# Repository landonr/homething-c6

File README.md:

<p align="center">
  <picture>
    <source media="(prefers-color-scheme: dark)" srcset="docs/readme-assets/homeThingLogoWhite.svg">
    
  </picture>
</p>

<h1 align="center">homeThing C6</h1>

<p align="center">
  An open source universal remote that can control anything.<br>
  For your TV, Sonos, Zigbee lights, and Home Assistant. No touchscreen, no apps, no daily charging.
</p>

<p align="center">
  <a href="https://landonr.github.io/homething-c6/"><b>landonr.github.io/homething-c6</b></a>
</p>

<p align="center">

</p>

<p align="center">
  <sub>Prototype and fab costs sponsored by <a href="https://pcbway.com/g/Xymq6O">PCBWay</a>. Boards arrive fully assembled, no soldering required.</sub>
  <br>
  
</p>

<p align="center"><sub>One button lights the fireplace, another controls the lights, and the rest control the TV. <a href="https://landonr.github.io/homething-c6/">Learn more</a></sub></p>

## What homeThing C6 does

- **Runs your TV.** It learns the IR codes from the remote you already have. Then the wheel and pad drive the TV.
- **Switches the lights.** A button talks straight to Zigbee lights and groups.
- **Any button, any device.** Each button can drive something different, for example a gas fireplace over Zigbee.
- **Sleeps on its own.** It sleeps between presses, with a target of about a month per charge.
- **No hub needed.** Presses go straight to your Zigbee lights and IR devices. They work without Wi-Fi, Home Assistant, or Zigbee2MQTT.
- **No flashing needed.** Set every button from the remote's own web page, in any browser. You do not edit YAML or rebuild the firmware.
- **Bluetooth keys too.** Pair it like a Bluetooth keyboard or gamepad, and send media keys to a computer, phone, or tablet.
- **Open source, all of it.** The board, the case, and the ESPHome firmware are in this repository.

## Specs

### One remote, no screen.

| Spec | Detail |
| --- | --- |
| **Controls** | Scroll wheel with 5-way pad, 11 assignable buttons |
| **Battery** | 1000 mAh LiPo, with a target of about a month per charge |
| **Charging** | USB-C |
| **Processor** | Seeed Studio XIAO ESP32-C6 |
| **Infrared** | Transmits, receives, and learns codes |
| **Status** | 6 RGB LEDs |
| **Case** | 3D printed, SLA or FDM |
| **Wireless** | Wi-Fi, BLE, Zigbee |

## Build one, or get one ready to go

The board arrives fully assembled, so there is no soldering. The board design, the firmware, and the case files are all open source in this repository, so you can build your own from scratch.

- **Case:** The [`case/` README](case/README.md) documents the enclosure files and assembly information.
- **Board:** The [`c6remote-kicad/` README](c6remote-kicad/README.md) documents the KiCad hardware source.
- **Firmware:** The [Make It Yours](#make-it-yours) section documents button assignment. [`c6remote.yaml`](c6remote.yaml) is the ESPHome configuration.
- **Scripts:** The [`scripts/` README](scripts/README.md) documents project utilities and generated assets.

<p align="center"><sub>V2 board and case</sub></p>

## Your smart home, on real buttons

### Control Anything

Pick it up, press a button, and the lights change. No phone to unlock, no app to open.

- **TV:** Learns the IR codes from the remote you already have, then sends them.
- **Music:** Controls Sonos over Wi-Fi, or pairs with a phone, tablet, or computer over BLE for media keys.
- **Lights:** Talks straight to Zigbee lights and groups.
- **Home Assistant:** Puts any action or script on a button.

<p align="center">
  <picture>
    <source media="(prefers-color-scheme: dark)" srcset="docs/readme-assets/remote-controls-annotated-dark.svg">
    
  </picture>
  <picture>
    <source media="(prefers-color-scheme: dark)" srcset="docs/readme-assets/remote-back-annotated-dark.svg">
    
  </picture>
</p>

## Make It Yours

### Every button is yours to set.

Open the remote's own web page from any browser on your network. Pick a button, then pick what it does: an IR code, a Zigbee light or group, a BLE media key, or a Home Assistant action. You can also assign buttons on the remote itself. No app, no cloud.

#### Button assignment ([more info](RECEIVER.md))

Open `http://homething-c6-xxxxxx.local/` in a browser. `xxxxxx` is the end of the remote's MAC address.
Home Assistant also shows this address as the **Web Page** entity.
To assign buttons on the remote itself, hold `SW9` for two seconds.
[`RECEIVER.md`](RECEIVER.md) has the full steps.
The page has no password, so use it only on a trusted network.

<p align="center"><sub>The Buttons tab with a Zigbee assignment, and the Config tab</sub></p>

## Built Your Way

### Case ([more info](case/README.md))

- Parametric 3D printed case in three versions: FDM, SLA, and SLA one-piece.
- The flat FDM front needs no support on its face.
- The SLA front has a shallow dish around the keys and the wheel. A translucent ring insert carries the light of the status LEDs.
- The SLA one-piece front is the SLA front with the ring insert fused in. It prints in clear resin, so the whole front glows.
- Optional Qwiic access: a flush cover with two breakaway bridges stays in place until you need the port.
- Assembly needs one M2 x 5 pan head screw at the grip end.

<p align="center"><sub>SLA front face</sub></p>

### Board ([more info](c6remote-kicad/README.md))

- Custom PCB built around the Seeed Studio XIAO ESP32-C6.
- Sleeps between presses and wakes on any button.

<p align="center">
  <picture>
    <source media="(prefers-color-scheme: dark)" srcset="docs/readme-assets/board-front-annotated-dark.svg">
    
  </picture>
  <picture>
    <source media="(prefers-color-scheme: dark)" srcset="docs/readme-assets/board-back-annotated-dark.svg">
    
  </picture>
</p>
<p align="center"><sub>PCB front and back</sub></p>

<p align="center"><sub>Copper top and bottom</sub></p>

| Ref | Part | Role |
| --- | --- | --- |
| `U1` | [Seeed Studio XIAO ESP32-C6](https://mm.digikey.com/Volume0/opasdata/d220001/medias/docus/8932/102010636.pdf) | Main module: Wi-Fi, BLE, Zigbee/Thread |
| `MK1` | [DMM-4026-B-I2S-R I2S microphone](https://api.puiaudio.com/filename/DMM-4026-B-I2S-R.pdf) | Audio input: PUI Audio bottom-port MEMS part on the back copper, hearing through a 0.5mm NPTH. `LR` and `CONFIG` tie to ground for left-channel output, `C5` decouples VDD and `R12` pulls `sd` down. It replaced the ICS-43434 on 2026-09-07, after three of the five rev-B microphones failed |
| `U2` | [TSOP6136 IR receiver](https://www.vishay.com/docs/82457/tsop61.pdf) | IR receive: Vishay Panhead SMD part on the back copper, listening out the top end wall. AGC1, the most permissive of Vishay's settings, which is what lets `remote_receiver` learn arbitrary remotes. VDD sits on the switched `ir_vdd` rail rather than straight on `+3.3V`, gated by `Q3` below |
| `D1`, `Q1` | [INL-3AHIR30 IR LED](http://www.inolux-corp.com/datasheet/IR/Emitter/3mm%20Lamp/INL-3AHIR30_V1.0.pdf) driven by [MMBT2222A](https://assets.nexperia.com/documents/data-sheet/MMBT2222A.pdf) | IR transmit; D1 leads hand-bent 90° to fire through the top-edge notch (see `BEND 90°` silk mark) |
| `U3` | [PCF8575DBR I2C GPIO expander](https://www.ti.com/lit/ds/symlink/pcf8575.pdf) | Button input fan-out |
| `SW1`–`SW11` | [TL3315NF160Q tactile switches](https://www.e-switch.com/wp-content/uploads/2022/06/TL3315.pdf) | Discrete buttons |
| `ENC1` | [Adafruit ANO rotary encoder](https://cdn-learn.adafruit.com/assets/assets/000/104/942/original/tsw.pdf) | Scroll wheel: encoder channels plus five switch signals |
| `D2`–`D7` | [XL-2020RGBC-WS2812B addressable LEDs](https://mm.digikey.com/Volume0/opasdata/d220001/medias/docus/8903/5962_XL-2020RGBC-WS2812B.pdf) | Status light ring of 6 round the scroll wheel, WS2812B protocol: `GPIO17` drives `D2` DIN, and DOUT cascades clockwise through `D3`, `D6`, `D4`, and `D5` to `D7`. VDD sits on the switched `led_vdd` rail rather than straight on `+3.3V`, gated by `Q2` below, with `C4` as the only bulk cap on the chain (see [`docs/timeline.md`](docs/timeline.md)) |
| `Q2`, `R10`, `C4` | [AO3401A P-channel MOSFET](https://www.aosmd.com/res/datasheets/AO3401A.pdf), 1M 0603 pull-up, 1µF X7R 0805 cap | LED rail load switch: high-side `Q2` gates `+3.3V` (source) onto `led_vdd` (drain) for `D2`–`D7`, gate net `led_en` on `U1` pad 11 (`GPIO18`/`D10`), driven low for rail on. `R10` pulls the gate to the source so the rail is off by default at boot while `GPIO18` floats as an input; `C4` is the mid-chain bulk cap on `led_vdd`. Cuts the ~3.0mA the six LEDs draw when dark to tens of µA (calculated, not yet measured). Firmware must hold `GPIO17` low or high-impedance whenever the rail is down, or DIN pushes current into the dead rail |
| `J1` | [Molex PicoBlade 53261-0271](https://www.molex.com/content/dam/molex/molex-dot-com/products/automated/en-us/salesdrawingpdf/532/53261/532610271_sd.pdf) | Battery connector, PicoBlade 1.25 mm right-angle SMD on the back copper. Its mouth faces `U1`. Pin 1 is BAT, next to the "+" silk. The cell plug is a `51021-0200` housing with `50079-8000` terminals. Cells with 1.25 mm plugs have no standard polarity, so some cells have reversed leads. Before you connect a cell, make sure that its polarity agrees with the silk |
| `J2` | [JST SM04B-SRSS-TB(LF)(SN)](https://www.jst-mfg.com/product/pdf/eng/eSH.pdf) | Qwiic I2C port, SH series right-angle SMD on the back copper. Its mouth faces the long edge opposite `U1`. A Qwiic device must not use `0x20`, the `U3` address |

The auto-generated BOM lives at [c6remote-kicad/export/c6remote-bom.csv](c6remote-kicad/export/c6remote-bom.csv). It tracks the latest repo state and is not release-validated.

#### Schematic

<p align="center">
  <a href="docs/readme-assets/schematic.svg">
    <picture>
      <source media="(prefers-color-scheme: dark)" srcset="docs/readme-assets/schematic-dark.svg">
      
    </picture>
  </a>
  <br>
  <sub>Open the <a href="docs/readme-assets/schematic.svg">full-size schematic</a> to read the part values and the net names.</sub>
</p>

## Status ([more info](docs/timeline.md))

The fabrication and bring-up history, the rev-B delivery, and the unit 1 versus current design comparison are in [`docs/timeline.md`](docs/timeline.md). Open work is in the [GitHub issues](https://github.com/landonr/homething-c6/issues). The power budget is in [`docs/power-budget.md`](docs/power-budget.md).

The factory test procedure for an assembled board is at [homeThing C6 Factory Test](https://landonr.github.io/homething-c6/factory-self-test.html). The board runs the factory firmware, and an operator watches the status LED ring at each step. The test needs no computer, and the page prints to PDF for the bench.

## Relationship to homeThing ([more info](https://github.com/landonr/homeThing))

This project grew out of [homeThing](https://github.com/landonr/homeThing) but has a narrower job: instead of a general smart display, it is a simple dedicated remote. It has no screen and more buttons, and is built on a custom PCB that is easy to build.

## License

This repository uses three licenses. A file uses the license of the row that contains its path.

| Path | License |
| --- | --- |
| The ESPHome configs (`c6remote*.yaml`, `secrets.example.yaml`, `partitions.csv`), the root C++ headers (`*.h`), `components/`, `scripts/`, and `.github/` | [GPL-3.0-or-later](LICENSE-GPL-3.0) |
| `c6remote-kicad/` (the schematic, the board, the symbol and footprint libraries, and the `export/` fabrication files), `kicad lib/`, and `case/` (the build123d model source, its checks, the board STEP and DXF files, and the meshes and STEP files that the model exports) | [CERN-OHL-S-2.0](LICENSE-CERN-OHL-S-2.0) |
| The documentation (`README.md`, `RECEIVER.md`, `ZIGBEE.md`, `TRANSMITTING.md`, and `docs/`, with the images in `docs/readme-assets/`), and `site/` | [CC-BY-4.0](LICENSE-CC-BY-4.0) |
| All other files, for example `AGENTS.md`, `.gitignore`, `.gitattributes`, `.mcp.json`, and `.vscode/` | [GPL-3.0-or-later](LICENSE-GPL-3.0) |

A firmware binary that you build from these configs links the GPL-3.0 C++ core of ESPHome. As a result, a distributed binary is GPL-3.0. Its source is this repository and the dependencies below.

For CERN-OHL-S-2.0, the Source Location of the hardware is <https://github.com/landonr/homething-c6>.

### Third-party files

These files keep their own licenses:

| File | Origin | License |
| --- | --- | --- |
| `case/fonts/DejaVuSans.ttf` | DejaVu fonts | Bitstream Vera license, see [`case/fonts/LICENSE`](case/fonts/LICENSE) |
| `scripts/assets/env-studio.hdr` | Poly Haven `studio_small_09` HDRI | CC0-1.0 |
| The Wi-Fi and Bluetooth icons in `site/index.html` | Feather icons | MIT |
| `kicad lib/Library.pretty/LED_D3.0mm_Horizontal_O1.27mm_Z2.0mm_IRBlack.kicad_mod`, and the `SW_TL3315NF160Q` and `TSOP61xx` symbols in `c6remote-kicad/Local.kicad_sym` | KiCad libraries | CC-BY-SA-4.0 with the [KiCad library exception](https://www.kicad.org/libraries/license/) |

Because of the KiCad library exception, CC-BY-SA-4.0 does not apply to a design that uses these items. The schematic and the board also contain stock KiCad symbols and footprints. The same exception applies to them.

These items are not in this repository:

- The KiCad 3D models are in a private repository. See `scripts/link-3dmodels.sh`.
- The build fetches these firmware dependencies:
  - ESPHome: MIT for the Python code, and GPL-3.0 for the C++ code.
  - ESP-IDF and `esp-zigbee-lib`: Apache-2.0.
  - `luar123/zigbee_esphome`: no license file yet. [Issue 119](https://github.com/luar123/zigbee_esphome/issues/119) asks for one.

The licenses do not give rights to trademarks, for example ESPHome, Home Assistant, Seeed Studio XIAO, Adafruit ANO, Discord, and GitHub. Some of these trademarks are in images, for example `site/assets/legacy/s3-video.jpg`.

# Includes
- <a href="https://esphome.io/">ESPHome</a>
- <a href="https://dejavu-fonts.github.io/">DejaVu Sans Bold</a>, used for the board silkscreen brand text
- [@luar123](https://github.com/luar123)'s <a href="https://github.com/luar123/zigbee_esphome">Zigbee ESPHome component</a>
- <a href="https://www.kicad.org/">KiCad</a>
- <a href="https://github.com/landonr/homeThing">homeThing</a>

# Sponsorship

## [PCBWay](https://pcbway.com/g/Xymq6O "PCBWay") sponsors 3D Printing and PCB assembly costs on this project during the prototyping phase! 
If you are interested in their awesome fabrication services please check them out.&nbsp; They offer 

3D prototyping,&nbsp;PCB design and assembly, as well as CNC metal fabrication.&nbsp; Costs are reasonable and the quality is as good as it gets.&nbsp; Thank you PCBWay for sponsoring us and other fun projects!

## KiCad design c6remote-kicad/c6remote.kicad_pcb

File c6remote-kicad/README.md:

# KiCad project

## Open the project

Open `c6remote.kicad_pro` in KiCad.
KiCad must resolve `../kicad lib/Library.pretty/` with the `Library` nickname.

The `sym-lib-table` file registers these symbol libraries:

- `dmm_4026_b_i2s_r`: The local `dmm_4026_b_i2s_r.kicad_sym` file contains the `MK1` microphone symbol.
- `Local`: The local `Local.kicad_sym` file contains the switch, IR receiver, XIAO ESP32-C6 module, and [Adafruit ANO rotary encoder](https://www.adafruit.com/product/5001) symbols.

### 3D models

The custom footprints reference their 3D models in `3dmodels/`.
This repository does not contain these models, because most are third-party files without a clear right to redistribute.
The models are in the private `c6remote-explode` repository.

Without the models, the KiCad 3D view shows bare pads for these parts.
The fabrication outputs, ERC, and DRC do not use the models.

If you have the `c6remote-explode` checkout, run `../scripts/link-3dmodels.sh` once for each clone or worktree.
The script links `3dmodels/` to the models in that checkout.
If the checkout is not at `~/dev/c6remote-explode`, set `EXPLODE` to its path.

## KiCad MCP

The repository uses the same KiCad MCP server with Codex and GitHub Copilot in VS Code:

- Codex workspace configuration: `../.mcp.json`
- VS Code workspace configuration: `../.vscode/mcp.json`

## Validation and fabrication

### Schematic-only agent workflow

Run this workflow from the repository root.
Use a unique session name for each schematic or custom-footprint edit loop.
The PCB must remain unchanged between `preflight` and `verify`.

```bash
./scripts/hw.py doctor
./scripts/hw.py preflight my-edit

# Inspect the baseline before an edit.
./scripts/hw.py inspect my-edit component U3
./scripts/hw.py inspect my-edit net sda
./scripts/hw.py inspect my-edit pin U3 14

# Run after every schematic or custom-footprint edit.
./scripts/hw.py quick my-edit

# Inspect the refreshed state and all baseline changes.
./scripts/hw.py inspect my-edit changes

# Run once before handoff.
./scripts/hw.py verify my-edit
./scripts/hw.py clean my-edit
```

Native KiCad ERC is authoritative.
Semantic analysis detects topology, BOM, metadata, findings, and custom-footprint regressions.

Use `--json` with `inspect` for stable structured output.
Use `--force` with `quick` or `inspect` to bypass reusable analysis.

Session artifacts stay in `.cache/hw/<session>/`.
The `preflight` command does not replace an existing session.
Reuse one session for repeated `inspect` and `quick` commands.
The session keeps its original baseline until you run `clean`.
If a session is old or incomplete, run `clean` and `preflight` again.

The tool refreshes stale inspection data before it prints results.
It reuses validated analysis and changed-footprint data when all fingerprints match.
It does not reuse failed or incomplete output.
It rejects simultaneous operations on one session.

The tool resolves `kicad-cli` from `KICAD_CLI`, `PATH`, or the macOS application bundle.
It resolves the analyzer from `KICAD_HAPPY_DIR`, shared, Codex, or Claude skill locations.
An invalid override stops discovery.
The `doctor` command prints each selected path.
The analyzer must emit schema 1.4.x.

If the analyzer is missing or incompatible, move or remove its existing destination.
Then install the pinned version:

```bash
python3 "${CODEX_HOME:-$HOME/.codex}/skills/.system/skill-installer/scripts/install-skill-from-github.py" --repo aklofas/kicad-happy --ref v2.2.0 --path skills/kicad
```

Exit code `0` means pass.
Exit code `1` means a design regression.
Exit code `2` means a tooling or configuration failure.

A PCB change makes `quick` and `inspect` fail before analysis starts.
The message explains that the session cannot validate PCB edits.
The `quick` command blocks only new deterministic analyzer errors.
The `verify` command always runs fresh native checks and stores outputs in the session cache.

### Native checks

Run these commands from this directory:

```bash
# Schematic ERC
/Applications/KiCad/KiCad.app/Contents/MacOS/kicad-cli sch erc c6remote.kicad_sch --exit-code-violations

# Board DRC
/Applications/KiCad/KiCad.app/Contents/MacOS/kicad-cli pcb drc c6remote.kicad_pcb --exit-code-violations

# Full board DRC with schematic parity and zone refill
/Applications/KiCad/KiCad.app/Contents/MacOS/kicad-cli pcb drc c6remote.kicad_pcb --schematic-parity --refill-zones --exit-code-violations
```

### Fabrication outputs

Regenerate all Gerber, drill, position, and BOM files in `export/`:

```bash
../scripts/regen-fab.sh
```

Regenerate only the BOM after you edit symbol sourcing fields:

```bash
../scripts/export-bom.sh
```

Use this script instead of the KiCad MCP `export_bom` tool.
The MCP tool uses a different schema and removes the custom sourcing columns.

### Board renders

Render reusable 2D board views in `renders/<format>/`:

```bash
../scripts/render-2d.sh
../scripts/render-2d.sh --side top
../scripts/render-2d.sh --side bottom --format pdf
```

### Interactive BOM

Generate the interactive HTML BOM for the pre-fabrication pin-1 check:

```bash
../scripts/gen-ibom.sh
```

The command writes the ignored `ibom.html` file in this directory.
The pre-commit hook also updates it when you stage `c6remote.kicad_pcb`.

Complete the [pre-fabrication checklist](../docs/pre-fab-checklist.md) before you order a board.

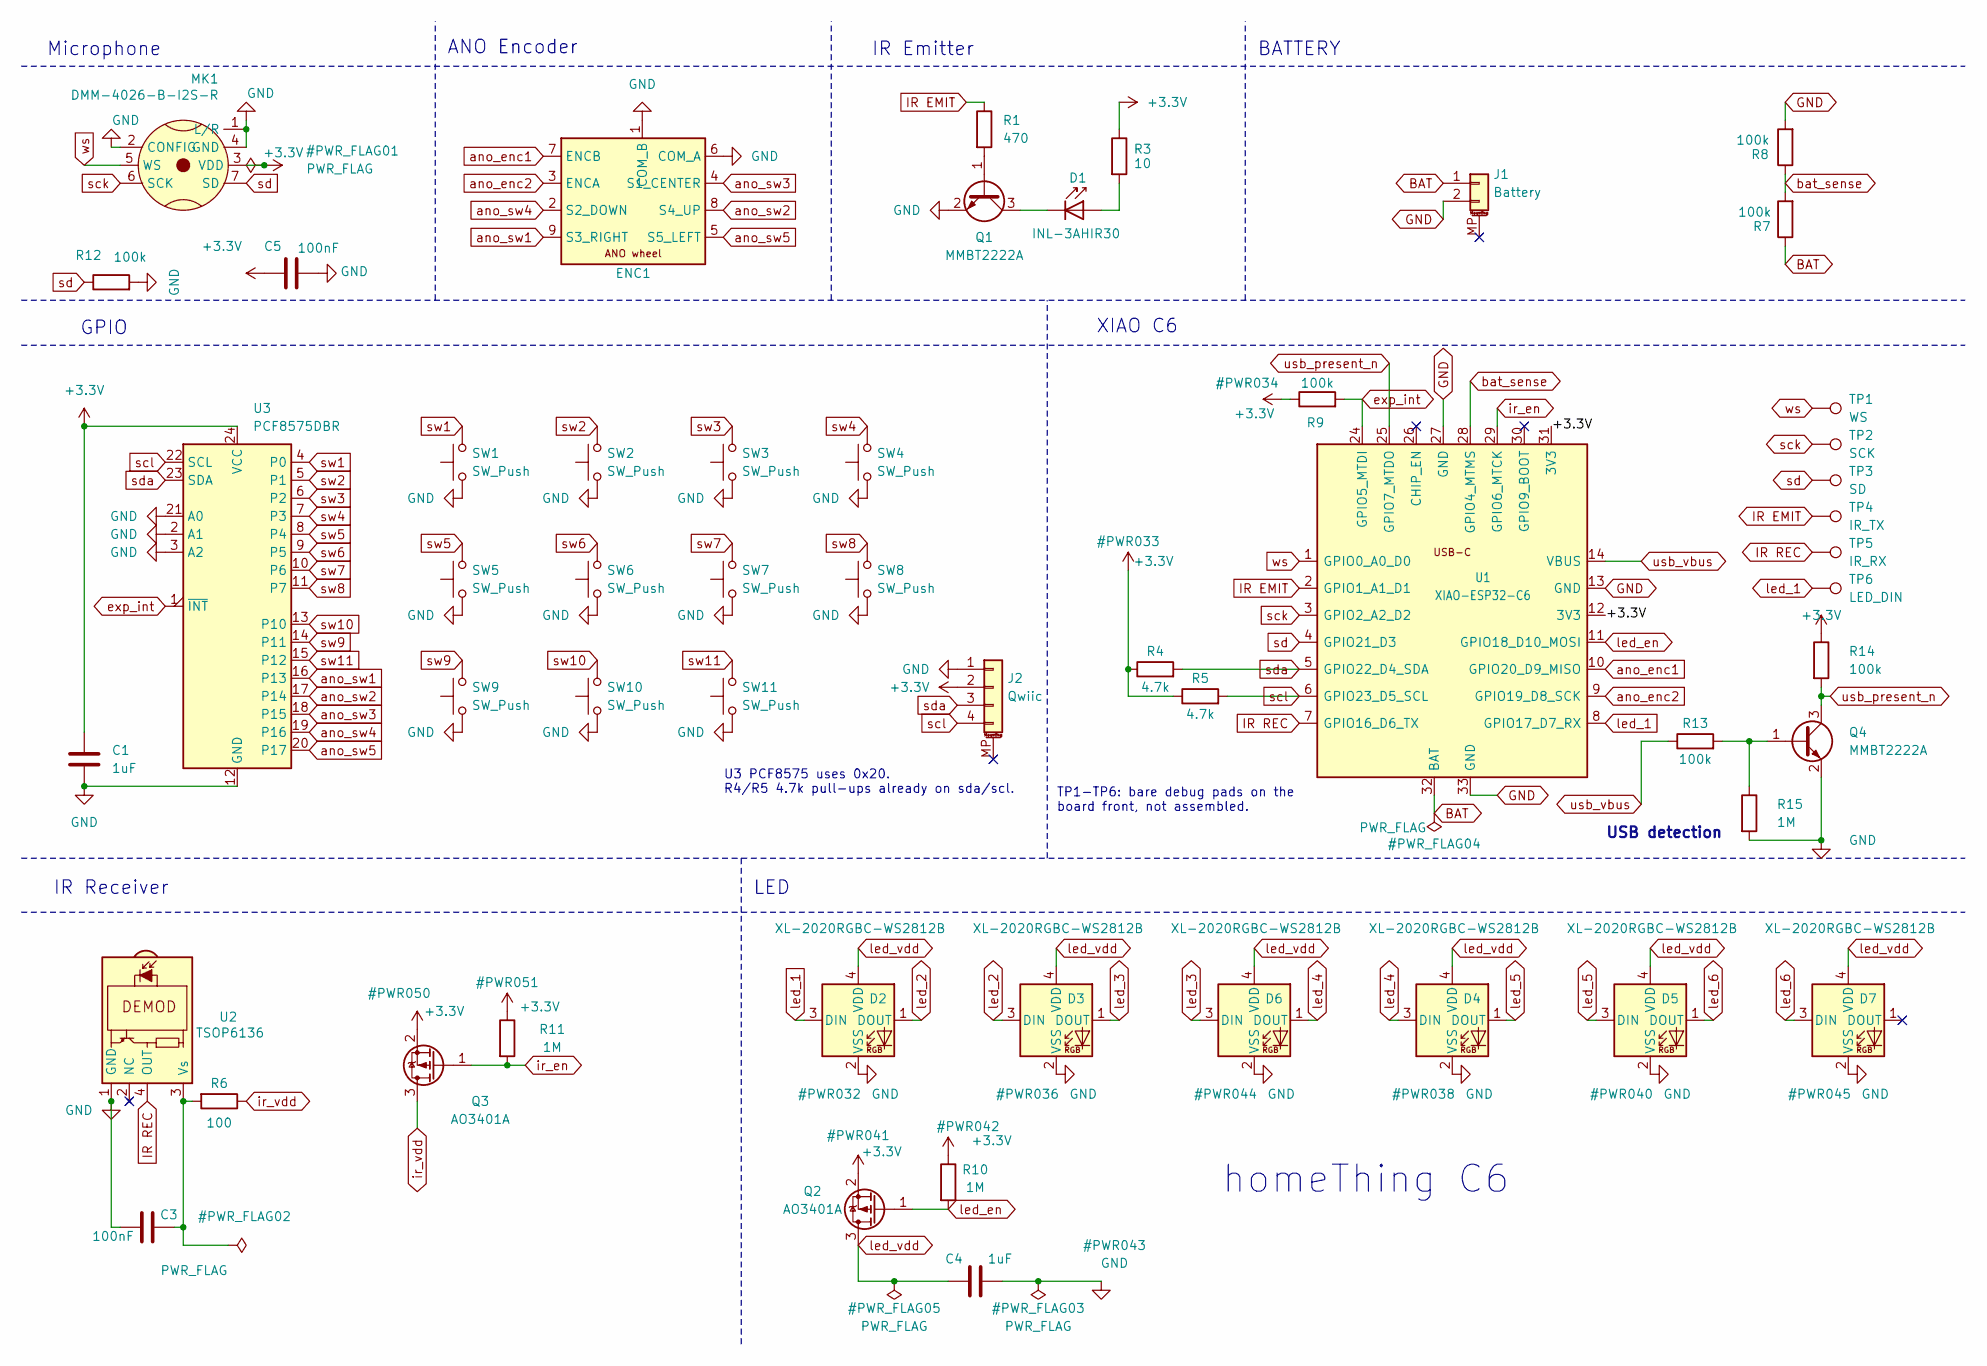
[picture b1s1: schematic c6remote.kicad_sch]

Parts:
C1, C4: 1uF; C_0805_2012Metric; MPN CC0805KKX7R9BB105
C3, C5: 100nF; C_0603_1608Metric; MPN CC0603KRX7R9BB104
D1: INL-3AHIR30; LED_D3.0mm_Horizontal_O1.27mm_Z2.0mm_IRBlack; MPN INL-3AHIR30
D2, D3, D4, D5, D6, D7: XL-2020RGBC-WS2812B; LED_XL-2020RGBC-WS2812B_PLCC4_2.0x2.0mm; MPN XL-2020RGBC-WS2812B
ENC1: ANO-Rotary-Encoder; MPN Adafruit 5001
J1: Battery; Molex_PicoBlade_53261-0271_1x02-1MP_P1.25mm_Horizontal; MPN 53261-0271
J2: Qwiic; JST_SH_SM04B-SRSS-TB_1x04-1MP_P1.00mm_Horizontal; MPN SM04B-SRSS-TB(LF)(SN)
MK1: DMM-4026-B-I2S-R; MIC_DMM-4026-B-I2S-R; MPN DMM-4026-B-I2S-R
Q1, Q4: MMBT2222A; SOT-23; MPN MMBT2222A,215
Q2, Q3: AO3401A; SOT-23; MPN AO3401A
R1: 470; R_0603_1608Metric; MPN RC0603FR-07470RL
R3: 10; R_0603_1608Metric; MPN RC0603FR-0710RL
R4, R5: 4.7k; R_0603_1608Metric; MPN RC0603FR-074K7L
R6: 100; R_0603_1608Metric; MPN RC0603FR-07100RL
R7, R8, R9, R12, R13, R14: 100k; R_0603_1608Metric; MPN RC0603FR-07100KL
R10, R11, R15: 1M; R_0603_1608Metric; MPN RC0603FR-071ML
SW1, SW2, SW3, SW4, SW5, SW6, SW7, SW8, SW9, SW10, SW11: SW_Push; SW_TL3315NF160Q; MPN TL3315NF160Q
TP1: WS; TestPoint_Pad_D1.0mm
TP2: SCK; TestPoint_Pad_D1.0mm
TP3: SD; TestPoint_Pad_D1.0mm
TP4: IR_TX; TestPoint_Pad_D1.0mm
TP5: IR_RX; TestPoint_Pad_D1.0mm
TP6: LED_DIN; TestPoint_Pad_D1.0mm
U1: XIAO-ESP32-C6; XIAO-ESP32-C6-SMD; MPN 113991254
U2: TSOP6136; Vishay_PANHEAD-4Pin_TopView; MPN TSOP6136TT
U3: PCF8575DBR; SSOP-24_5.3x8.2mm_P0.65mm; MPN PCF8575DBR

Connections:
IR EMIT: R1.1, TP4.1 (1_1), U1.2 (GPIO1_A1_D1)
IR REC: TP5.1 (1_1), U1.7 (GPIO16_D6_TX), U2.4 (OUT)
unnamed: D1.2 (A), R3.2
unnamed: D1.1 (K), Q1.3 (C)
unnamed: Q1.1 (B), R1.2
unnamed: Q4.1 (B), R13.2, R15.1
ano_enc1: ENC1.7 (ENCB), U1.10 (GPIO20_D9_MISO)
ano_enc2: ENC1.3 (ENCA), U1.9 (GPIO19_D8_SCK)
ano_sw1: ENC1.9 (S3_RIGHT), U3.16 (P13)
ano_sw2: ENC1.8 (S4_UP), U3.17 (P14)
ano_sw3: ENC1.4 (S1_CENTER), U3.18 (P15)
ano_sw4: ENC1.2 (S2_DOWN), U3.19 (P16)
ano_sw5: ENC1.5 (S5_LEFT), U3.20 (P17)
bat_sense: R7.2, R8.1, U1.28 (GPIO4_MTMS)
exp_int: R9.2, U1.24 (GPIO5_MTDI), U3.1 (~INT)
ir_en: Q3.1 (G), R11.2, U1.29 (GPIO6_MTCK)
ir_vdd: Q3.3 (D), R6.1
led_1: D2.3 (DIN), TP6.1 (1_1), U1.8 (GPIO17_D7_RX)
led_2: D2.1 (DOUT), D3.3 (DIN)
led_3: D3.1 (DOUT), D6.3 (DIN)
led_4: D4.3 (DIN), D6.1 (DOUT)
led_5: D4.1 (DOUT), D5.3 (DIN)
led_6: D5.1 (DOUT), D7.3 (DIN)
led_en: Q2.1 (G), R10.2, U1.11 (GPIO18_D10_MOSI)
sck: MK1.6 (SCK), TP2.1 (1_1), U1.3 (GPIO2_A2_D2)
scl: J2.4, R5.2, U1.6 (GPIO23_D5_SCL), U3.22 (SCL)
sd: MK1.7 (SD), R12.1, TP3.1 (1_1), U1.4 (GPIO21_D3)
sda: J2.3, R4.2, U1.5 (GPIO22_D4_SDA), U3.23 (SDA)
sw1: SW1.3, SW1.4, U3.4 (P0)
sw2: SW2.3, SW2.4, U3.5 (P1)
sw3: SW3.3, SW3.4, U3.6 (P2)
sw4: SW4.3, SW4.4, U3.7 (P3)
sw5: SW5.3, SW5.4, U3.8 (P4)
sw6: SW6.3, SW6.4, U3.9 (P5)
sw7: SW7.3, SW7.4, U3.10 (P6)
sw8: SW8.3, SW8.4, U3.11 (P7)
sw9: SW9.3, SW9.4, U3.14 (P11)
sw10: SW10.3, SW10.4, U3.13 (P10)
sw11: SW11.3, SW11.4, U3.15 (P12)
usb_present_n: Q4.3 (C), R14.2, U1.25 (GPIO7_MTDO)
usb_vbus: R13.1, U1.14 (VBUS)
ws: MK1.5 (WS), TP1.1 (1_1), U1.1 (GPIO0_A0_D0)

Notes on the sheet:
BATTERY
U3 PCF8575 uses 0x20. R4/R5 4.7k pull-ups already on sda/scl.
XIAO C6
homeThing C6
IR Emitter
ANO Encoder
TP1-TP6: bare debug pads on the board front, not assembled.
IR Receiver
USB detection
Microphone
GPIO
LED

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
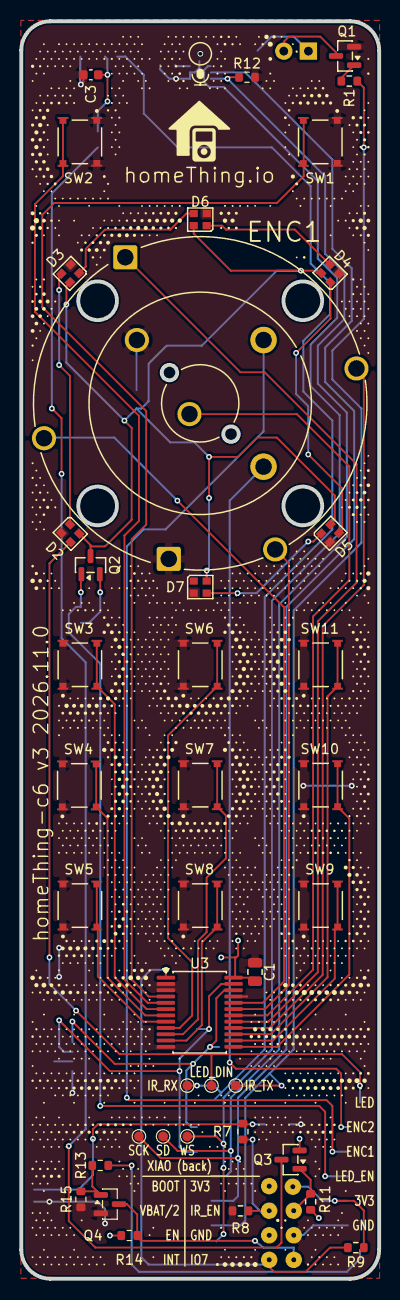
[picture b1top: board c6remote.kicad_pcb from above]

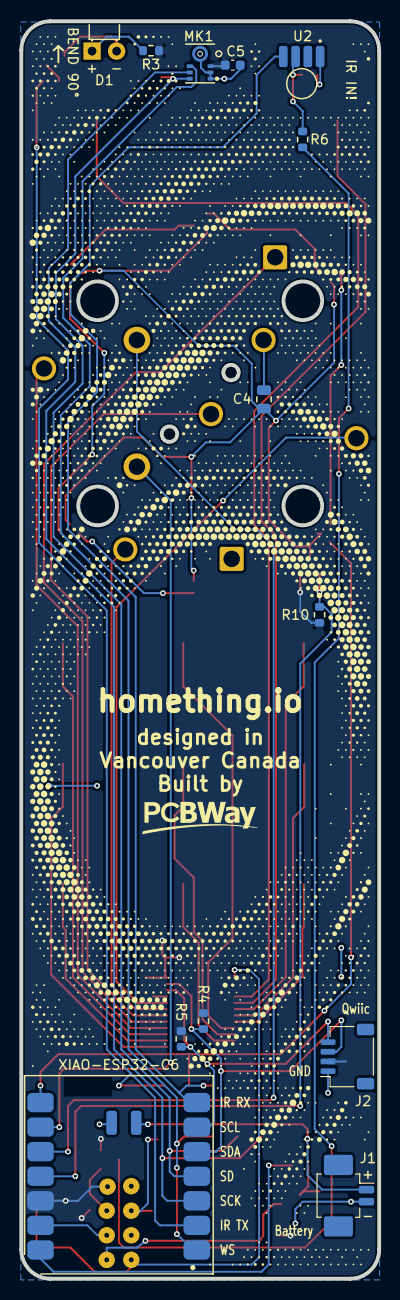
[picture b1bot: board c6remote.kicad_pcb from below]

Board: 2 copper layers, 37.0 x 130.0 mm, 53 parts (13 on the bottom side), 47 nets.

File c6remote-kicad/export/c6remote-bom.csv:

"Reference","Qty","Value","Footprint","Datasheet","Description","Manufacturer","MPN","Digikey","Mouser","Adafruit","LCSC"
"C1, C4","2","1uF","Capacitor_SMD:C_0805_2012Metric","","Capacitor: 1uF 50V X7R 0805 (decoupling),Capacitor: 1uF 50V X7R 0805 (led_vdd bulk, local charge for D2-D7)","Yageo","CC0805KKX7R9BB105","https://www.digikey.com/en/products/detail/yageo/CC0805KKX7R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","https://www.mouser.com/ProductDetail/YAGEO/CC0805KKX7R9BB105","",""
"C3, C5","2","100nF","Capacitor_SMD:C_0603_1608Metric","~","Capacitor: 100nF 50V X7R 0603 (MK1 VDD decoupling),Capacitor: 100nF 50V X7R 0603 (U2 TSOP Vs filter)","Yageo","CC0603KRX7R9BB104","https://www.digikey.com/en/products/detail/yageo/CC0603KRX7R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","https://www.mouser.com/ProductDetail/YAGEO/CC0603KRX7R9BB104","",""
"D1","1","INL-3AHIR30","Library:LED_D3.0mm_Horizontal_O1.27mm_Z2.0mm_IRBlack","http://www.inolux-corp.com/datasheet/IR/Emitter/3mm%20Lamp/I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","IR Emitter: 940nm 3mm THT LED (leads bent 90 deg to top-edge notch = IR aperture)","Inolux","INL-3AHIR30","https://www.digikey.com/en/products/detail/inolux/INL-3AHIR3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","https://www.mouser.com/ProductDetail/Inolux/INL-3AHIR30","",""
"D2, D3, D4, D5, D6, D7","6","XL-2020RGBC-WS2812B","Library:LED_XL-2020RGBC-WS2812B_PLCC4_2.0x2.0mm","https://mm.digikey.com/Volume0/opasdata/d220001/medias/docus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","RGB LED: XL-2020RGBC-WS2812B addressable, integrated controller, 5mA/ch, VDD 3.5-5.5V, 2020 PLCC4","XINGLIGHT","XL-2020RGBC-WS2812B","https://www.digikey.com/en/products/detail/xinglight/XL-2020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","","","https://www.lcsc.com/product-detail/C5349955.html"
"ENC1","1","","Library:ANO-Rotary-Encoder","https://cdn-learn.adafruit.com/assets/assets/000/104/942/ori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","Rotary Encoder: ANO directional navigation + scroll wheel","Adafruit","Adafruit 5001","https://www.digikey.com/en/products/detail/adafruit-industri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","https://www.mouser.com/ProductDetail/Adafruit/5001","https://www.adafruit.com/product/5001",""
"J1","1","Battery","Connector_Molex:Molex_PicoBlade_53261-0271_1x02-1MP_P1.25mm_Horizontal","https://www.molex.com/content/dam/molex/molex-dot-com/produc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","Battery connector, Molex PicoBlade 1.25 mm 2-pin right-angle SMD. Pin 1 BAT (+), pin 2 GND","Molex","53261-0271","https://www.digikey.com/en/products/detail/molex/0532610271/699107","https://www.mouser.com/ProductDetail/Molex/53261-0271","","https://www.lcsc.com/product-detail/C177225.html"
"J2","1","Qwiic","Connector_JST:JST_SH_SM04B-SRSS-TB_1x04-1MP_P1.00mm_Horizontal","https://www.jst-mfg.com/product/pdf/eng/eSH.pdf","Qwiic I2C connector, JST SH 1.0 mm 4-pin right-angle: 1 GND, 2 +3.3V, 3 SDA, 4 SCL","JST","SM04B-SRSS-TB(LF)(SN)","https://www.digikey.com/en/products/detail/jst-sales-america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","https://www.mouser.com/ProductDetail/JST-Commercial/SM04B-SR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","","https://www.lcsc.com/product-detail/C160404.html"
"MK1","1","DMM-4026-B-I2S-R","Library:MIC_DMM-4026-B-I2S-R","https://api.puiaudio.com/filename/DMM-4026-B-I2S-R.pdf","Microphone: I2S MEMS, 24-bit, omnidirectional bottom port, 4.0x3.0mm","PUI Audio","DMM-4026-B-I2S-R","https://www.digikey.com/en/products/detail/pui-audio-inc/DMM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","https://www.mouser.com/ProductDetail/PUI-Audio/DMM-4026-B-I2S-R","",""
"Q1, Q4","2","MMBT2222A","Package_TO_SOT_SMD:SOT-23","https://assets.nexperia.com/documents/data-sheet/MMBT2222A.pdf","Transistor: NPN 40V 600mA SOT-23 (IR LED driver),Transistor: NPN 40V 600mA SOT-23 (USB detection)","Nexperia","MMBT2222A,215","https://www.digikey.com/en/products/detail/nexperia-usa-inc/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","https://www.mouser.com/ProductDetail/Nexperia/MMBT2222A215","",""
"Q2, Q3","2","AO3401A","Package_TO_SOT_SMD:SOT-23","https://www.aosmd.com/res/datasheets/AO3401A.pdf","Transistor: P-channel MOSFET -30V -4A SOT-23 (ir_vdd high-side switch),Transistor: P-channel MOSFET -30V -4A SOT-23 (led_vdd high-side switch)","Alpha & Omega Semiconductor","AO3401A","https://www.digikey.com/en/products/detail/alpha-omega-semic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","","","https://www.lcsc.com/product-detail/C15127.html"
"R1","1","470","Resistor_SMD:R_0603_1608Metric","","Resistor: 470R 1% 0.1W 0603 (Q1 base)","Yageo","RC0603FR-07470RL","https://www.digikey.com/en/products/detail/yageo/RC0603FR-07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","https://www.mouser.com/ProductDetail/YAGEO/RC0603FR-07470RL","",""
"R3","1","10","Resistor_SMD:R_0603_1608Metric","~","Resistor: 10R 1% 0.1W 0603 (D1 IR LED current limit)","Yageo","RC0603FR-0710RL","https://www.digikey.com/en/products/detail/yageo/RC0603FR-07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","https://www.mouser.com/ProductDetail/YAGEO/RC0603FR-0710RL","",""
"R4, R5","2","4.7k","Resistor_SMD:R_0603_1608Metric","~","Resistor: 4.7k 1% 0.1W 0603 (I2C SDA/SCL pull-up)","Yageo","RC0603FR-074K7L","https://www.digikey.com/en/products/detail/yageo/RC0603FR-07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","https://www.mouser.com/ProductDetail/YAGEO/RC0603FR-074K7L","",""
"R6","1","100","Resistor_SMD:R_0603_1608Metric","~","Resistor: 100R 1% 0.1W 0603 (U2 TSOP Vs filter)","Yageo","RC0603FR-07100RL","https://www.digikey.com/en/products/detail/yageo/RC0603FR-07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","https://www.mouser.com/ProductDetail/YAGEO/RC0603FR-07100RL","",""
"R7, R8, R9, R12, R13, R14","6","100k","Resistor_SMD:R_0603_1608Metric","~","Resistor: 100k 1% 0.1W 0603 (MK1 SD pull-down),Resistor: 100k 1% 0.1W 0603 (USB detection base resistor),Resistor: 100k 1% 0.1W 0603 (USB detection collector pull-up),Resistor: 100k 1% 0.1W 0603 (batt sense divider / INT pull-up)","Yageo","RC0603FR-07100KL","https://www.digikey.com/en/products/detail/yageo/RC0603FR-07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","https://www.mouser.com/ProductDetail/YAGEO/RC0603FR-07100KL","",""
"R10, R11, R15","3","1M","Resistor_SMD:R_0603_1608Metric","~","Resistor: 1M 1% 0.1W 0603 (Q2 gate pull-up, holds led_vdd off by default),Resistor: 1M 1% 0.1W 0603 (Q3 gate pull-up, holds ir_vdd off by default),Resistor: 1M 1% 0.1W 0603 (USB detection base pull-down)","Yageo","RC0603FR-071ML","https://www.digikey.com/en/products/detail/yageo/RC0603FR-07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","https://www.mouser.com/ProductDetail/YAGEO/RC0603FR-071ML","",""
"SW1, SW2, SW3, SW4, SW5, SW6, SW7, SW8, SW9, SW10, SW11","11","SW_Push","Library:SW_TL3315NF160Q","https://www.e-switch.com/wp-content/uploads/2022/06/TL3315.pdf","Switch: tactile pushbutton SPST-NO SMD","E-Switch","TL3315NF160Q","https://www.digikey.com/en/products/detail/e-switch/TL3315NF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","https://www.mouser.com/ProductDetail/E-Switch/TL3315NF160Q","",""
"U1","1","XIAO-ESP32-C6","Library:XIAO-ESP32-C6-SMD","https://mm.digikey.com/Volume0/opasdata/d220001/medias/docus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","MCU Module: Seeed XIAO ESP32-C6, Wi-Fi 6 / BLE 5 / Zigbee / Thread","Seeed Studio","113991254","https://www.digikey.com/en/products/detail/seeed-technology-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","https://www.mouser.com/ProductDetail/Seeed-Studio/113991254","",""
"U2","1","TSOP6136","Library:Vishay_PANHEAD-4Pin_TopView","https://www.vishay.com/docs/82457/tsop61.pdf","IR Receiver: remote control module, 36kHz","Vishay","TSOP6136TT","https://www.digikey.com/en/products/detail/vishay-semiconduc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","https://www.mouser.com/ProductDetail/Vishay-Semiconductors/T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","",""
"U3","1","PCF8575DBR","Package_SO:SSOP-24_5.3x8.2mm_P0.65mm","https://www.ti.com/lit/ds/symlink/pcf8575.pdf","GPIO Expander: 16-bit I2C, SSOP-24","Texas Instruments","PCF8575DBR","https://www.digikey.com/en/products/detail/texas-instruments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","https://www.mouser.com/ProductDetail/Texas-Instruments/PCF8575DBR","",""

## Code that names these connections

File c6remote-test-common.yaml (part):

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#
# Pin map (c6remote.kicad_sch):
#   GPIO0  ws              GPIO16 IR REC        GPIO21 sd (I2S data)
#   GPIO1  IR EMIT         GPIO17 led_1 (D2-D5) GPIO22 sda
#   GPIO2  sck             GPIO18 led_en (D10)  GPIO23 scl
#   GPIO4  bat_sense /2    GPIO19 ano_enc2
#   GPIO5  exp_int (nINT)  GPIO20 ano_enc1
#   GPIO6  ir_en           GPIO7  usb_present_n (current design)
#
# led_en gates Q2, a high-side P-FET feeding led_vdd on D2-D5: low powers the
# rail, and R10 1M holds it off while GPIO18 floats. ir_en gates Q3 the same way
# for ir_vdd on U2, but defaults on, since the receiver is useless unpowered.
#
# GPIO7 is unconnected on rev-B but carries usb_present_n on the current design.
# IR REC uses GPIO16, outside the GPIO0-7 deep-sleep wake range.

# Defaults; version files override (main config wins per packages docs).
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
